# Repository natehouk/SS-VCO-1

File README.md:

# SS-VCO-1
VCO based on the AS3340-VCO.

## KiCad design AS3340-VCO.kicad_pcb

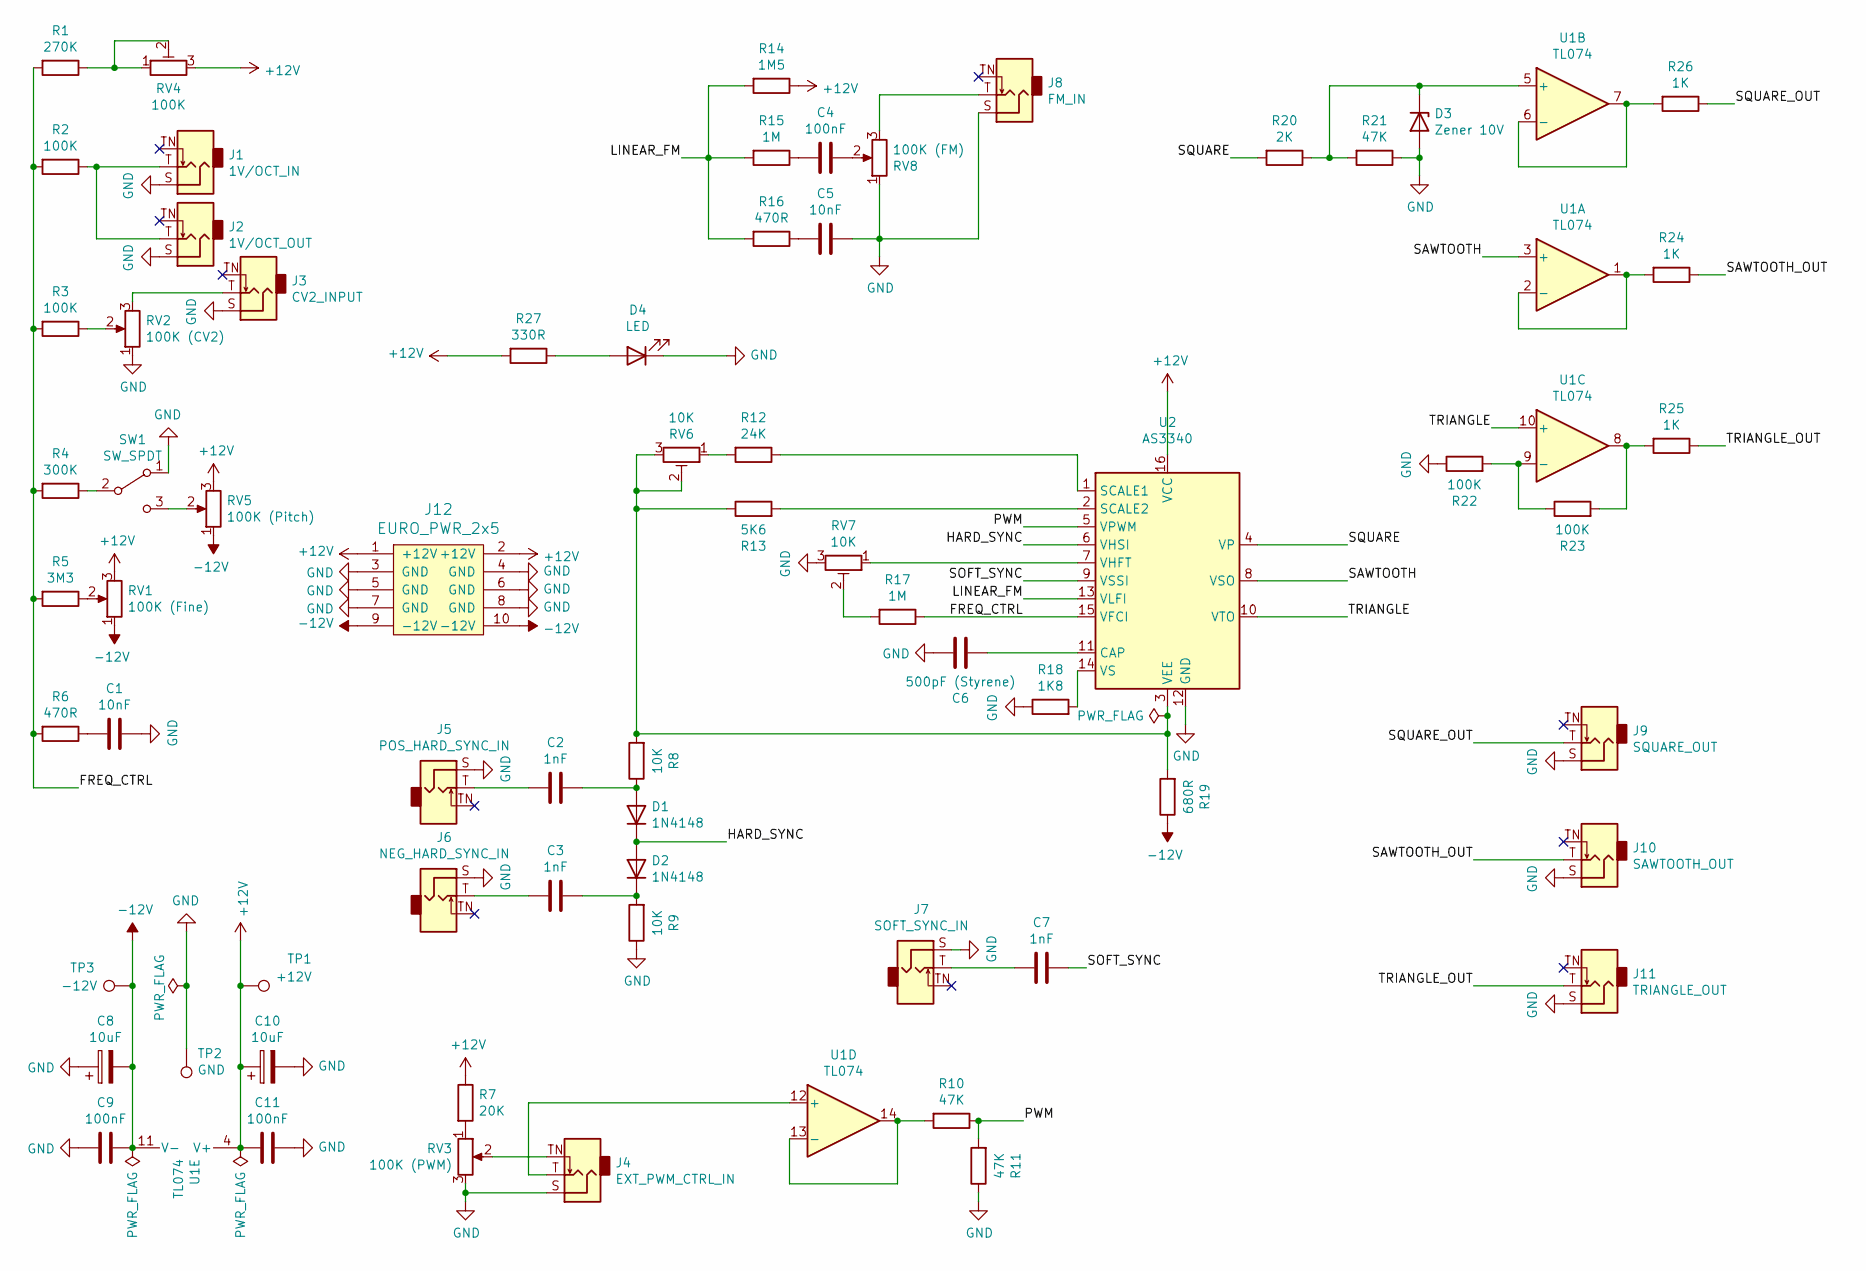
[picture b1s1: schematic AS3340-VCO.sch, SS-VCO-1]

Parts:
C1, C5: 10nF; C_0603_1608Metric
C2, C3, C7: 1nF; C_0603_1608Metric
C4, C9, C11: 100nF; C_0603_1608Metric
C6: 500pF (Styrene); C_Disc_D7.5mm_W2.5mm_P5.00mm
C8, C10: 10uF; CP_Radial_D5.0mm_P2.50mm
D1, D2: 1N4148; D_DO-35_SOD27_P7.62mm_Horizontal
D3: Zener 10V; D_DO-35_SOD27_P7.62mm_Horizontal
D4: LED; D_0603_1608Metric
J1: 1V/OCT_IN; Jack_3.5mm_QingPu_WQP-PJ398SM_Vertical_CircularHoles
J2: 1V/OCT_OUT; Jack_3.5mm_QingPu_WQP-PJ398SM_Vertical_CircularHoles
J3: CV2_INPUT; Jack_3.5mm_QingPu_WQP-PJ398SM_Vertical_CircularHoles
J4: EXT_PWM_CTRL_IN; Jack_3.5mm_QingPu_WQP-PJ398SM_Vertical_CircularHoles
J5: POS_HARD_SYNC_IN; Jack_3.5mm_QingPu_WQP-PJ398SM_Vertical_CircularHoles
J6: NEG_HARD_SYNC_IN; Jack_3.5mm_QingPu_WQP-PJ398SM_Vertical_CircularHoles
J7: SOFT_SYNC_IN; Jack_3.5mm_QingPu_WQP-PJ398SM_Vertical_CircularHoles
J8: FM_IN; Jack_3.5mm_QingPu_WQP-PJ398SM_Vertical_CircularHoles
J9: SQUARE_OUT; Jack_3.5mm_QingPu_WQP-PJ398SM_Vertical_CircularHoles
J10: SAWTOOTH_OUT; Jack_3.5mm_QingPu_WQP-PJ398SM_Vertical_CircularHoles
J11: TRIANGLE_OUT; Jack_3.5mm_QingPu_WQP-PJ398SM_Vertical_CircularHoles
J12: EURO_PWR_2x5; 3M_2510-6002UB
R1: 270K; R_0603_1608Metric
R2, R3, R22, R23: 100K; R_0603_1608Metric
R4: 300K; R_0603_1608Metric
R5: 3M3; R_0603_1608Metric
R6, R16: 470R; R_0603_1608Metric
R7: 20K; R_0603_1608Metric
R8, R9: 10K; R_0603_1608Metric
R10, R11, R21: 47K; R_0603_1608Metric
R12: 24K; R_0603_1608Metric
R13: 5K6; R_0603_1608Metric
R14: 1M5; R_0603_1608Metric
R15, R17: 1M; R_0603_1608Metric
R18: 1K8; R_0603_1608Metric
R19: 680R; R_0603_1608Metric
R20: 2K; R_0603_1608Metric
R24, R25, R26: 1K; R_0603_1608Metric
R27: 330R; R_0603_1608Metric
RV1: 100K (Fine); Potentiometer_Alpha_RD901F-40-00D_Single_Vertical
RV2: 100K (CV2); Potentiometer_Alpha_RD901F-40-00D_Single_Vertical
RV3: 100K (PWM); Potentiometer_Alpha_RD901F-40-00D_Single_Vertical
RV4: 100K; TRIM_3266W-1-102LF
RV5: 100K (Pitch); Potentiometer_Alpha_RD901F-40-00D_Single_Vertical
RV6, RV7: 10K; TRIM_3266W-1-102LF
RV8: 100K (FM); Potentiometer_Alpha_RD901F-40-00D_Single_Vertical
SW1: SW_SPDT; SW_Toggle_Blue_wSlots
TP1: +12V; TestPoint_Pad_4.0x4.0mm
TP2: GND; TestPoint_Pad_4.0x4.0mm
TP3: -12V; TestPoint_Pad_4.0x4.0mm
U1: TL074; DIP-14_W7.62mm_Socket
U2: AS3340; DIP-16_W7.62mm_Socket

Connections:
+12V: C10.1, C11.2, J12.1 (+12V), J12.2 (+12V), R7.1, R14.1, R27.2, RV1.3, RV4.3, RV5.3, TP1.1, U1.4 (V+), U2.16 (VCC)
-12V: C8.2, C9.1, J12.9 (-12V), J12.10 (-12V), R19.1, RV1.1, RV5.1, TP3.1, U1.11 (V-)
/FREQ_CTRL: R1.2, R2.2, R3.2, R4.2, R5.2, R6.2, R17.1, U2.15 (VFCI)
/HARD_SYNC: D1.1 (K), D2.2 (A), U2.6 (VHSI)
/LINEAR_FM: R14.2, R15.2, R16.2, U2.13 (VLFI)
/PWM: R10.1, R11.2, U2.5 (VPWM)
/SAWTOOTH: U1.3 (+), U2.8 (VSO)
/SAWTOOTH_OUT: J10.T, R24.1
/SOFT_SYNC: C7.1, U2.9 (VSSI)
/SQUARE: R20.2, U2.4 (VP)
/SQUARE_OUT: J9.T, R26.1
/TRIANGLE: U1.10 (+), U2.10 (VTO)
/TRIANGLE_OUT: J11.T, R25.1
GND: C1.1, C5.1, C6.1, C8.1, C9.2, C10.2, C11.1, D3.2 (A), D4.1 (K), J1.S, J2.S, J3.S, J4.S, J5.S, J6.S, J7.S, J8.S, J9.S, J10.S, J11.S, J12.3 (GND), J12.4 (GND), J12.5 (GND), J12.6 (GND), J12.7 (GND), J12.8 (GND), R9.1, R11.1, R18.1, R21.1, R22.1, RV2.1, RV3.3, RV7.3, RV8.1, SW1.1 (A), TP2.1, U2.12 (GND)
unnamed: C1.2, R6.1
unnamed: C2.1, D1.2 (A), R8.1
unnamed: C2.2, J5.T
unnamed: C3.1, D2.1 (K), R9.2
unnamed: C3.2, J6.T
unnamed: C4.1, RV8.2
unnamed: C4.2, R15.1
unnamed: C5.2, R16.1
unnamed: C6.2, U2.11 (CAP)
unnamed: C7.2, J7.T
unnamed: D3.1 (K), R20.1, R21.2, U1.5 (+)
unnamed: D4.2 (A), R27.1
unnamed: J1.T, J2.T, R2.1
unnamed: J3.T, RV2.3
unnamed: J4.T, U1.12 (+)
unnamed: J4.TN, RV3.2
unnamed: J8.T, RV8.3
unnamed: R1.1, RV4.1, RV4.2
unnamed: R3.1, RV2.2
unnamed: R4.1, SW1.2 (B)
unnamed: R5.1, RV1.2
unnamed: R7.2, RV3.1
unnamed: R10.2, U1.13 (-), U1.14
unnamed: R12.1, U2.1 (SCALE1)
unnamed: R12.2, RV6.1
unnamed: R8.2, R13.1, R19.2, RV6.2, RV6.3, U2.3 (VEE)
unnamed: R13.2, U2.2 (SCALE2)
unnamed: R17.2, RV7.2
unnamed: R18.2, U2.14 (VS)
unnamed: R22.2, R23.1, U1.9 (-)
unnamed: R23.2, R25.2, U1.8
unnamed: R24.2, U1.1, U1.2 (-)
unnamed: R26.2, U1.6 (-), U1.7
unnamed: RV5.2, SW1.3 (C)
unnamed: RV7.1, U2.7 (VHFT)

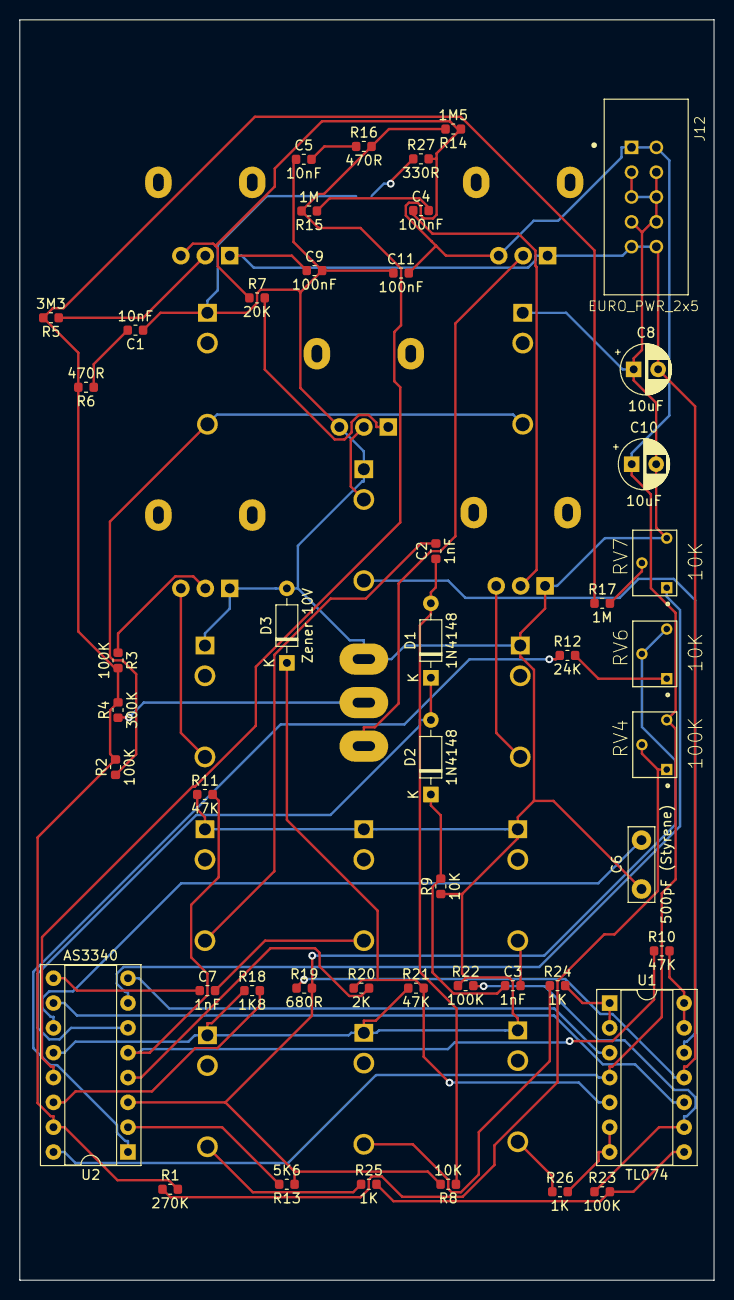
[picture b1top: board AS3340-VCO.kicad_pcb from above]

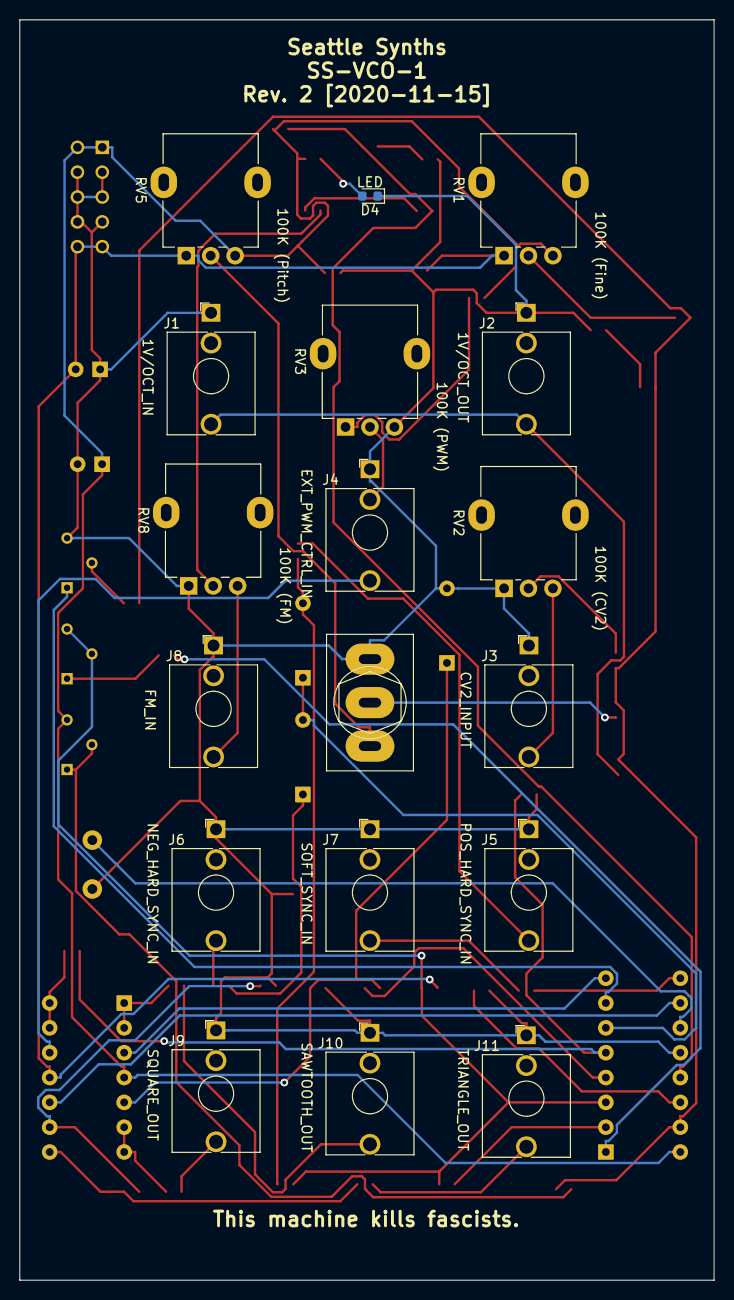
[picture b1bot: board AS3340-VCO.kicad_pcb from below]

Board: 2 copper layers, 71.0 x 128.9 mm, 69 parts (18 on the bottom side), 49 nets.

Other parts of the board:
BOTTOM_LEFT_MOUNT: MountingHole_3.2mm_M3_Oval
BOTTOM_RIGHT_MOUNT: MountingHole_3.2mm_M3_Oval
TOP_LEFT_MOUNT: MountingHole_3.2mm_M3_Oval
TOP_RIGHT_MOUNT: MountingHole_3.2mm_M3_Oval

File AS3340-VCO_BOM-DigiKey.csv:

"Manufacturer Part Number","Manufacturer","Digi-Key Part Number","Customer Reference","Reference Designator","Packaging","Part Status","Quantity","Unit Price","Extended Price","Quantity Available","Mfg Std Lead Time","Description","RoHS Status","Lead Free Status","REACH Status"
"MBA02040C3300FCT00","Vishay Beyschlag/Draloric/BC Components","BC3292CT-ND","","R27","Cut Tape (CT)","Active","1","0.22000","$0.22","2884","8 Weeks","RES 330 OHM 0.4W 1% AXIAL","ROHS3 Compliant","Lead free","Not Available"
"SFR25H0004700FR500","Vishay Beyschlag/Draloric/BC Components","56-SFR25H0004700FR500CT-ND","","R6 R16","Cut Tape (CT)","Active","2","0.17000","$0.34","3588","15 Weeks","RES 470 OHM 1/2W 1% AXIAL","ROHS3 Compliant","Lead free","Not Available"
"MBA02040C6800FCT00","Vishay Beyschlag/Draloric/BC Components","BC3284CT-ND","","R19","Cut Tape (CT)","Active","1","0.22000","$0.22","7577","8 Weeks","RES 680 OHM 0.4W 1% AXIAL","ROHS3 Compliant","Lead free","Not Available"
"SFR25H0001001FR500","Vishay Beyschlag/Draloric/BC Components","BC4391CT-ND","","R24 R25 R26","Cut Tape (CT)","Active","3","0.17000","$0.51","2412","15 Weeks","RES 1K OHM 1/2W 1% AXIAL","ROHS3 Compliant","Lead free","Not Available"
"MBA02040C1801FC100","Vishay Beyschlag/Draloric/BC Components","BC3467CT-ND","","R18","Cut Tape (CT)","Active","1","0.40000","$0.40","2165","9 Weeks","RES 1.8K OHM 0.4W 1% AXIAL","ROHS3 Compliant","Lead free","Not Available"
"SFR25H0002001FR500","Vishay Beyschlag/Draloric/BC Components","BC4404CT-ND","","R20","Cut Tape (CT)","Active","1","0.17000","$0.17","3948","15 Weeks","RES 2K OHM 1/2W 1% AXIAL","ROHS3 Compliant","Lead free","Not Available"
"MBB02070C5601FCT00","Vishay Beyschlag/Draloric/BC Components","BC3836CT-ND","","R13","Cut Tape (CT)","Active","1","0.26000","$0.26","12255","15 Weeks","RES 5.6K OHM 0.6W 1% AXIAL","ROHS3 Compliant","Lead free","Not Available"
"SFR25H0004702FR500","Vishay Beyschlag/Draloric/BC Components","56-SFR25H0004702FR500CT-ND","","R10 R11 R21","Cut Tape (CT)","Active","3","0.17000","$0.51","3715","15 Weeks","RES 47K OHM 1/2W 1% AXIAL","ROHS3 Compliant","Lead free","Not Available"
"MBA02040C3003FC100","Vishay Beyschlag/Draloric/BC Components","BC4441CT-ND","","R4","Cut Tape (CT)","Active","1","0.40000","$0.40","1096","8 Weeks","RES 300K OHM 1% 0.4W AXIAL","ROHS3 Compliant","Lead free","Not Available"
"SFR2500001002FR500","Vishay Beyschlag/Draloric/BC Components","PPC10.0KYCT-ND","","R8 R9","Cut Tape (CT)","Active","2","0.14000","$0.28","54225","15 Weeks","RES 10K OHM 0.4W 1% AXIAL","ROHS3 Compliant","Lead free","Not Available"
"SFR2500002002FR500","Vishay Beyschlag/Draloric/BC Components","PPC20.0KYCT-ND","","R7","Cut Tape (CT)","Active","1","0.14000","$0.14","8991","15 Weeks","RES 20K OHM 0.4W 1% AXIAL","ROHS3 Compliant","Lead free","Not Available"
"RNMF14FTC24K0","Stackpole Electronics Inc","S24KCACT-ND","","R12","Cut Tape (CT)","Active","1","0.10000","$0.10","6736","20 Weeks","RES 24K OHM 1/4W 1% AXIAL","ROHS3 Compliant","Lead free","REACH Unaffected"
"SFR16S0001003FR500","Vishay Beyschlag/Draloric/BC Components","PPC100KXCT-ND","","R2 R3 R22 R23","Cut Tape (CT)","Active","4","0.19000","$0.76","7291","18 Weeks","RES 100K OHM 1/2W 1% AXIAL","ROHS3 Compliant","Lead free","Not Available"
"SFR2500002703FR500","Vishay Beyschlag/Draloric/BC Components","PPC270KYCT-ND","","R1","Cut Tape (CT)","Discontinued at Digi-Key","1","0.14000","$0.14","1758","Not Available","RES 270K OHM 0.4W 1% AXIAL","ROHS3 Compliant","Lead free","Not Available"
"MBB02070C1504FCT00","Vishay Beyschlag/Draloric/BC Components","BC3622CT-ND","","R14","Cut Tape (CT)","Active","1","0.29000","$0.29","9171","8 Weeks","RES 1.5M OHM 0.6W 1% AXIAL","ROHS3 Compliant","Lead free","Not Available"
"SFR2500001004FR500","Vishay Beyschlag/Draloric/BC Components","PPC1.00MYCT-ND","","R15 R17","Cut Tape (CT)","Active","2","0.14000","$0.28","18070","15 Weeks","RES 1M OHM 0.4W 1% AXIAL","ROHS3 Compliant","Lead free","Not Available"
"MBB02070C3304FCT00","Vishay Beyschlag/Draloric/BC Components","BC3749CT-ND","","R5","Cut Tape (CT)","Active","1","0.29000","$0.29","5927","8 Weeks","RES 3.3M OHM 0.6W 1% AXIAL","ROHS3 Compliant","Lead free","Not Available"
"89210","NTE Electronics, Inc","2368-89210-ND","","C2 C3 C7","Bag","Active","25","0.11000","$2.75","150","Not Available","CAP-CER DISC 1000PF 50V","ROHS3 Compliant","Not Available","Not Available"
"89310","NTE Electronics, Inc","2368-89310-ND","","C1 C5","Bag","Active","25","0.15000","$3.75","2275","Not Available","CAP-CER DISC 10 000PF 50V","ROHS3 Compliant","Not Available","Not Available"
"89410","NTE Electronics, Inc","2368-89410-ND","","C4 C9 C11","Bag","Active","25","0.22000","$5.50","876","Not Available","CAP-CER .10UF 50V","ROHS3 Compliant","Not Available","Not Available"
"90150","NTE Electronics, Inc","2368-90150-ND","","C6","Bag","Active","25","0.17000","$4.25","767","Not Available","CAP-CER DISC 500PF 1KV","ROHS3 Compliant","Not Available","Not Available"
"1N4148","NTE Electronics, Inc","2368-1N4148-ND","","D1 D2","Bag","Active","25","0.05000","$1.25","42122","Not Available","D-SI 100PRV .01A","ROHS3 Compliant","Not Available","Not Available"
"151051RS11000","Würth Elektronik","732-5016-ND","","D4","Bulk","Active","1","0.16000","$0.16","5782","10 Weeks","LED RED DIFFUSED 5MM ROUND T/H","ROHS3 Compliant","Lead free","REACH Unaffected"
"1N5240BTR","ON Semiconductor","1N5240BFSCT-ND","","D3","Cut Tape (CT)","Active","1","0.14000","$0.14","21357","18 Weeks","DIODE ZENER 10V 500MW DO35","ROHS3 Compliant","Lead free","REACH Unaffected"
"61201021621","Würth Elektronik","732-2094-ND","","","Tray","Active","1","0.45000","$0.45","15887","14 Weeks","CONN HEADER VERT 10POS 2.54MM","ROHS3 Compliant","Lead free","REACH Unaffected"
"PT10LV10-103A2020-S","Amphenol Piher Sensing Systems","1993-1116-ND","","","Bulk","Active","1","0.47000","$0.47","11503","6 Weeks","POT 10K OHM LINEAR","ROHS3 Compliant","Lead free","Not Available"
"PT10LV10-104A2020-PM-S","Amphenol Piher Sensing Systems","1993-1082-ND","","","Bulk","Active","1","0.47000","$0.47","2900","7 Weeks","POT 100K OHM LINEAR","ROHS3 Compliant","Lead free","Not Available"
"54-302PC","NTE Electronics, Inc","2368-54-302PC-ND","","","Bag","Active","1","1.49000","$1.49","163","Not Available","SW-TOGGLE SPDT 5A","ROHS3 Compliant","Not Available","Not Available"
"860020572003","Würth Elektronik","732-8937-1-ND","","","Cut Tape (CT)","Active","1","0.10000","$0.10","2290","20 Weeks","CAP ALUM 10UF 20% 35V RADIAL","ROHS3 Compliant","Lead free","REACH Unaffected"
"TL074CN","Texas Instruments","296-1777-ND","","","Tube","Active","1","0.65000","$0.65","3455","6 Weeks","IC OPAMP JFET 4 CIRCUIT 14DIP","ROHS3 Compliant","Lead free","REACH Unaffected"
"P0915N-FC15BR100K","TT Electronics/BI","987-1709-ND","","","Tray","Active","5","1.36000","$6.80","4171","12 Weeks","POT 100K OHM 1/20W PLASTIC LIN","ROHS3 Compliant","Lead free","REACH Unaffected"

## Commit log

2020-11-01 Update page settings.
2020-11-01 Add LICENSE
2020-11-04 Refactor
2020-11-15 Rev. 1
2020-12-04 Revv. 2
2020-12-05 Rev. 2
